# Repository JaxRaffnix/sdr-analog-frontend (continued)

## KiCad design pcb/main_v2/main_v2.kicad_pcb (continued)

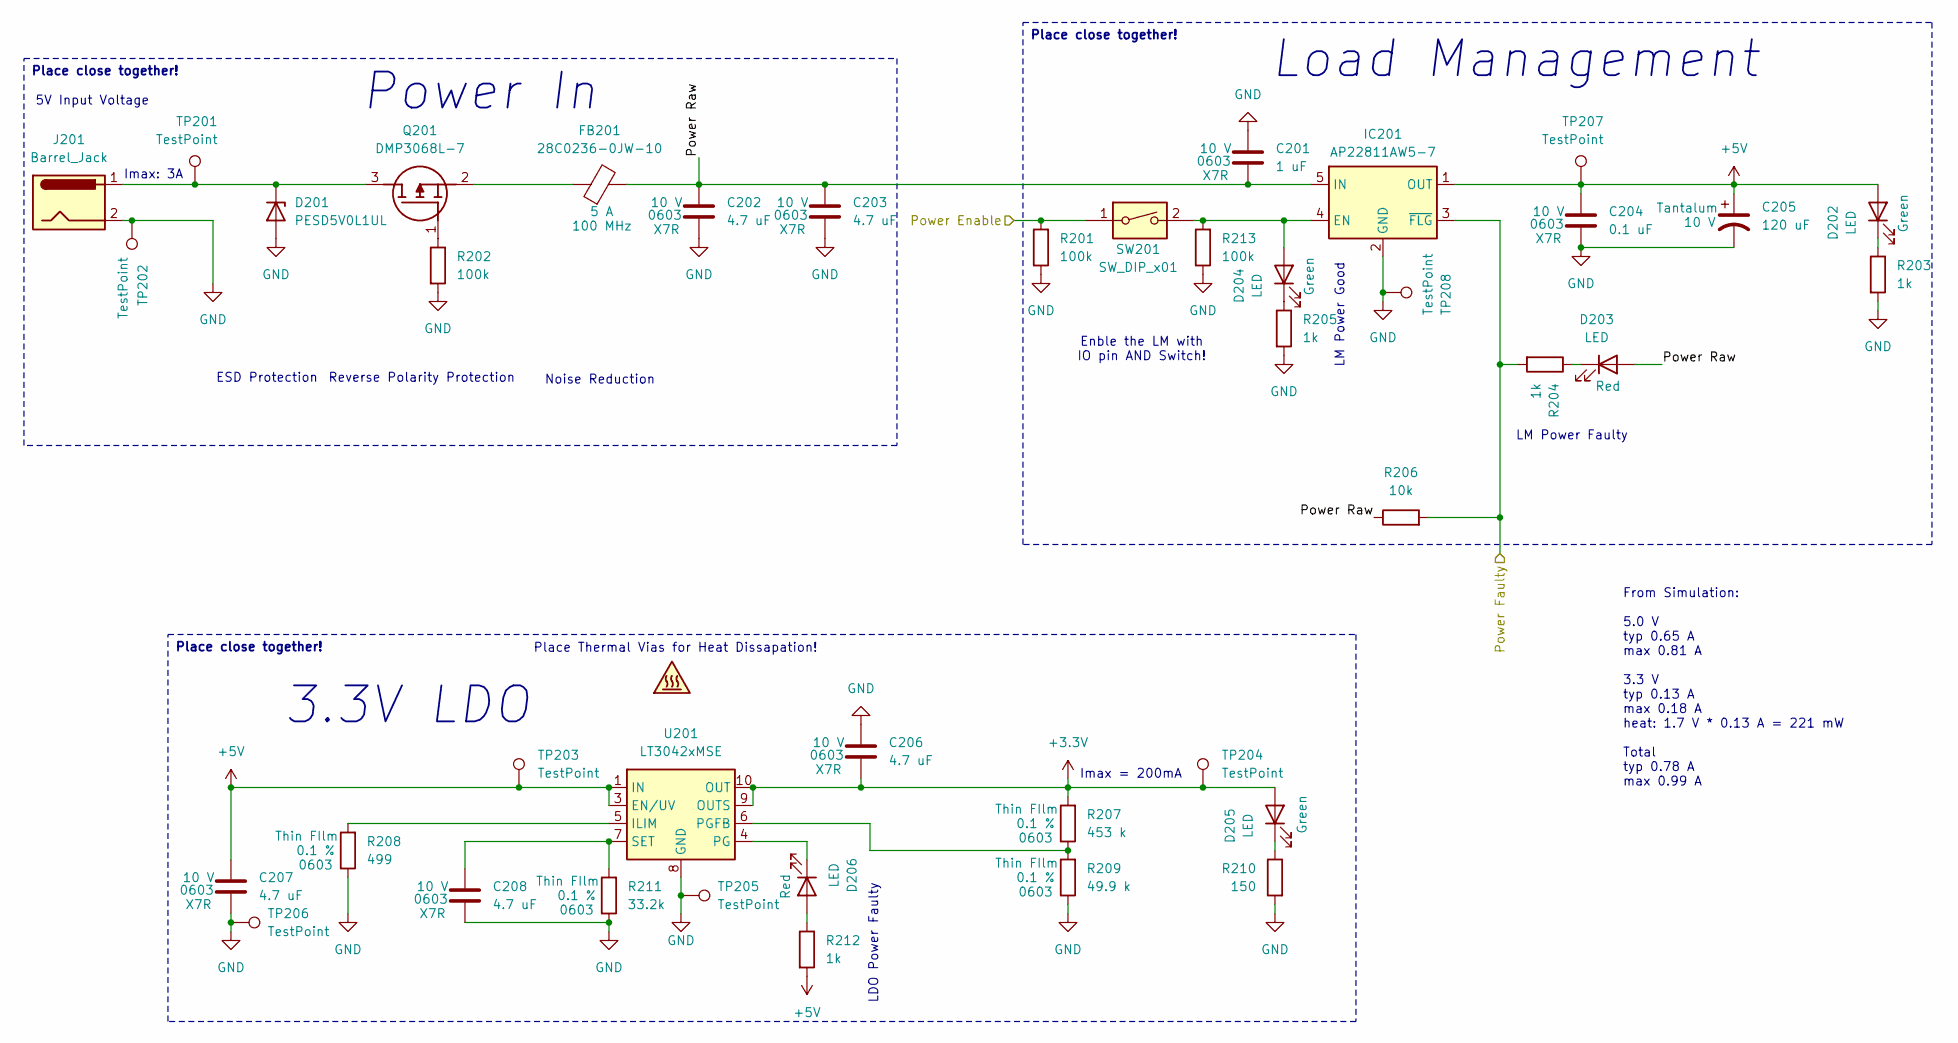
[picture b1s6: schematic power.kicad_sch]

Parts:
C201: 1 uF; C_0603_1608Metric; Voltage 10 V
C202, C203, C206, C207, C208: 4.7 uF; C_0603_1608Metric; Voltage 10 V
C204: 0.1 uF; C_0603_1608Metric; Voltage 10 V
C205: 120 uF; CP_EIA-6032-20_AVX-F; Voltage 10 V
D201: PESD5V0L1UL; D_SOD-882
D202, D203, D204, D205, D206: LED; LED_0805_2012Metric
FB201: 28C0236-0JW-10; LairdTech_28C0236-0JW-10
IC201: AP22811AW5-7; SOT-23-5; Mouser Part Number 621-AP22811AW5-7
J201: Barrel_Jack; BarrelJack_CUI_PJ-063AH_Horizontal_CircularHoles
Q201: DMP3068L-7; SOT96P240X115-3N; Mouser Part Number 621-DMP3068L-7
R201, R202, R213: 100k; R_0603_1608Metric
R203, R204, R205, R212: 1k; R_0603_1608Metric
R206: 10k; R_0603_1608Metric
R207: 453 k; R_0603_1608Metric; Tolerance 0.1 %
R208: 499; R_0603_1608Metric; Tolerance 0.1 %
R209: 49.9 k; R_0603_1608Metric; Tolerance 0.1 %
R210: 150; R_0603_1608Metric
R211: 33.2k; R_0603_1608Metric; Tolerance 0.1 %
SW201: SW_DIP_x01; SW_DIP_SPSTx01_Slide_6.7x4.1mm_W6.73mm_P2.54mm_LowProfile_J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
TP201, TP202, TP203, TP204, TP205, TP206, TP207, TP208: TestPoint; TestPoint_Pad_D1.0mm
U201: LT3042xMSE; MSOP-10-1EP_3x3mm_P0.5mm_EP1.68x1.88mm

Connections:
+3.3V: C206.2, D205.2 (A), R207.2, TP204.1 (1_1), U201.9 (OUTS), U201.10 (OUT); also elsewhere on the board
+5V: C204.1, C205.1, C207.1, D202.2 (A), IC201.1 (OUT), R212.2, TP203.1 (1_1), TP207.1 (1_1), U201.1 (IN), U201.2 (IN), U201.3 (EN/UV); also elsewhere on the board
/IO Interface/Power Enable: R201.2, SW201.1; also elsewhere on the board
/IO Interface/Power Faulty Out: IC201.3 (~FLG), R204.2, R206.2; also elsewhere on the board
/power/Power Raw: C201.2, C202.1, C203.1, D203.2 (A), FB201.2, IC201.5 (IN), R206.1
GND: C201.1, C202.2, C203.2, C204.2, C205.2, C206.1, C207.2, C208.2, D201.2 (A), IC201.2 (GND), J201.2, R201.1, R202.2, R203.2, R205.2, R208.1, R209.1, R210.2, R211.1, R213.1, TP202.1 (1_1), TP205.1 (1_1), TP206.1 (1_1), TP208.1 (1_1), U201.8 (GND), U201.11 (GND); also elsewhere on the board
unnamed: D201.1 (K), J201.1, Q201.3 (D), TP201.1 (1_1)
unnamed: D202.1 (K), R203.1
unnamed: D203.1 (K), R204.1
unnamed: D204.2 (A), IC201.4 (EN), R213.2, SW201.2
unnamed: D204.1 (K), R205.1
unnamed: D205.1 (K), R210.1
unnamed: D206.2 (A), R212.1
unnamed: D206.1 (K), U201.4 (PG)
unnamed: Q201.1 (G), R202.1
unnamed: FB201.1, Q201.2 (S)
unnamed: R208.2, U201.5 (ILIM)
unnamed: R207.1, R209.2, U201.6 (PGFB)
unnamed: C208.1, R211.2, U201.7 (SET)

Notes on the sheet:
Power In
From Simulation: 5.0 V typ 0.65 A max 0.81 A 3.3 V typ 0.13 A max 0.18 A heat: 1.7 V * 0.13 A = 221 mW Total typ 0.78 A max 0.99 A
ESD Protection
LM Power Faulty
Load Management
Imax = 200mA
3.3V LDO
LDO Power Faulty
Imax: 3A
LM Power Good
Reverse Polarity Protection
Enble the LM with IO pin AND Switch!
Place Thermal Vias for Heat Dissapation!
Noise Reduction
5V Input Voltage
Place close together!

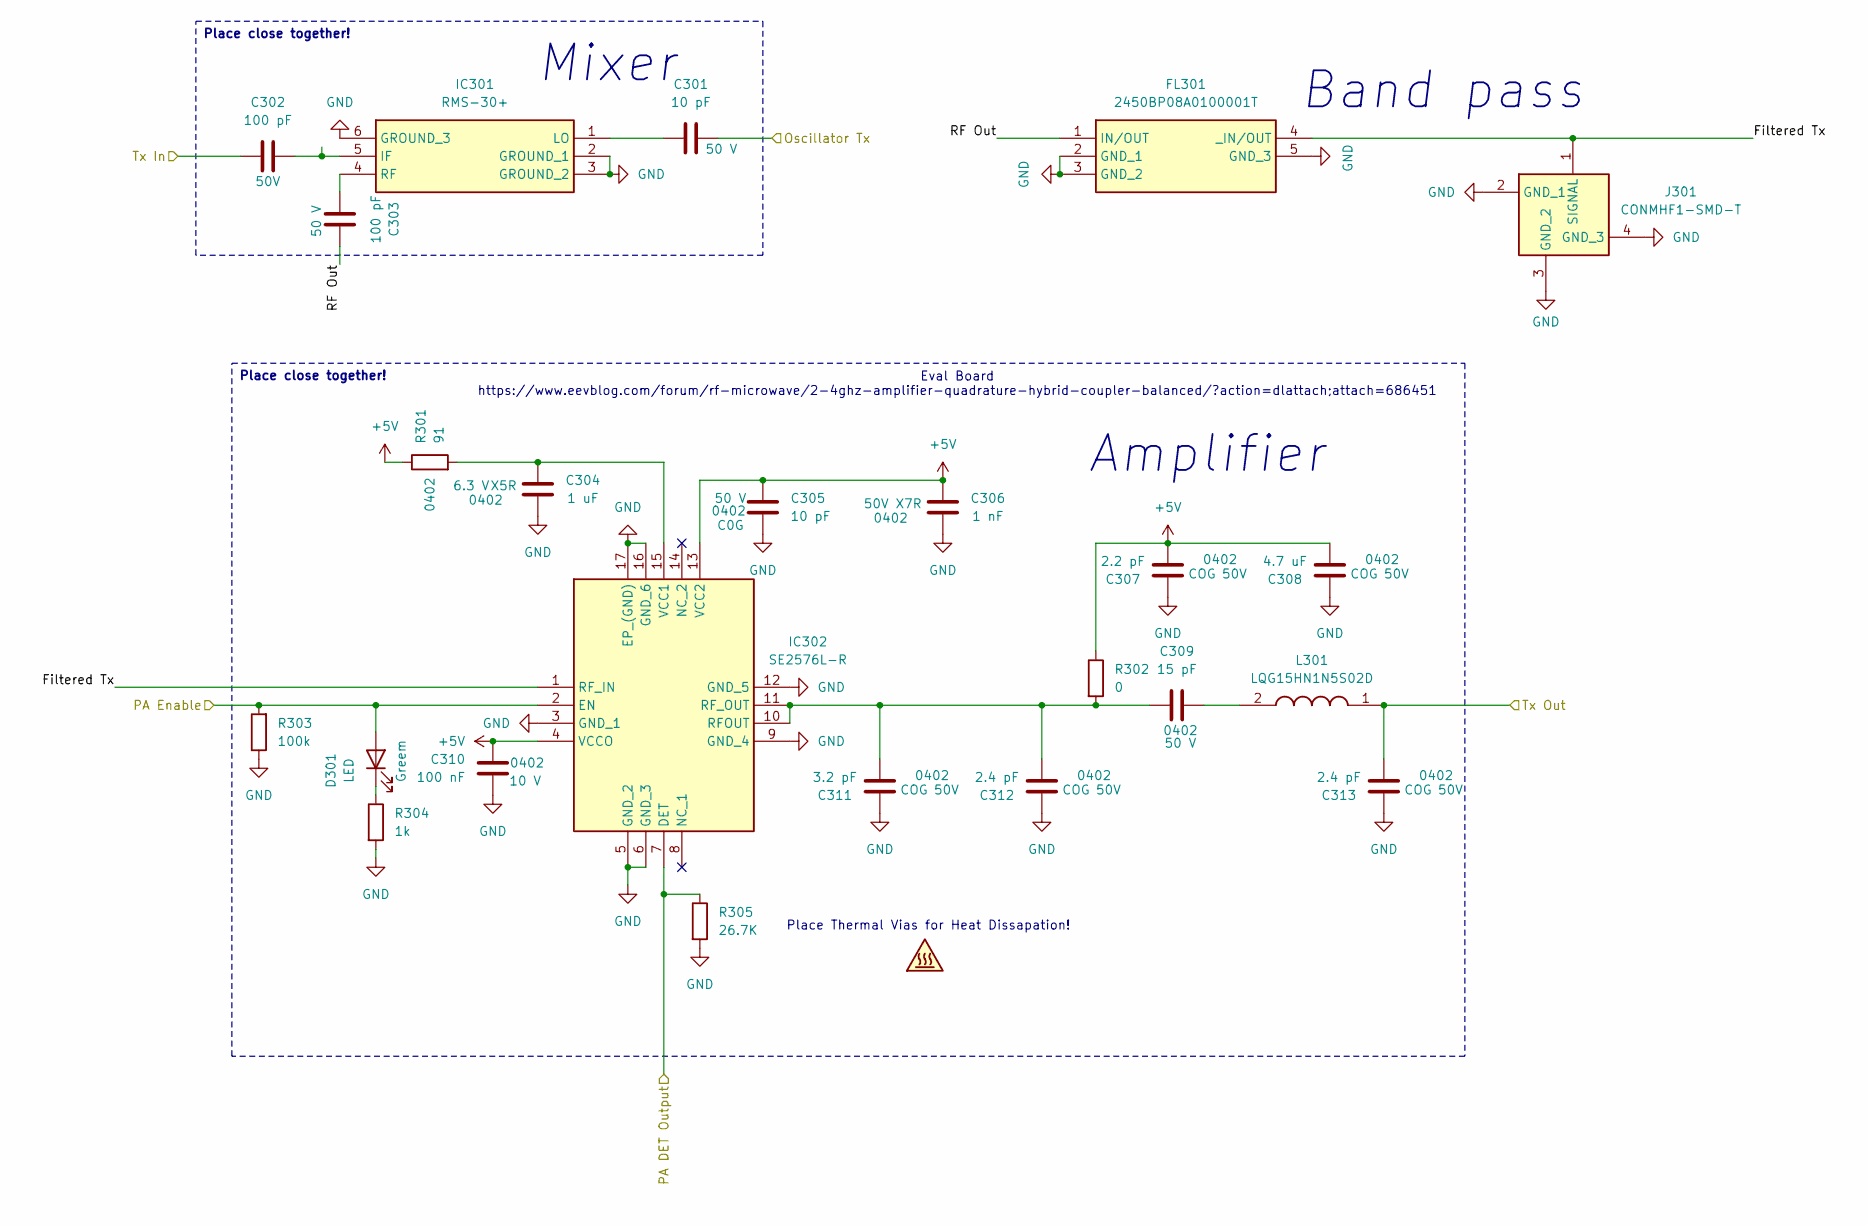
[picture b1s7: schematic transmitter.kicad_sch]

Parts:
C301, C305: 10 pF; C_0402_1005Metric; Voltage 50 V
C302: 100 pF; C_0402_1005Metric; Voltage 50V
C303: 100 pF; C_0402_1005Metric; Voltage 50 V
C304: 1 uF; C_0402_1005Metric; Tolerance 10 %; Voltage 6.3 V
C306: 1 nF; C_0402_1005Metric; Tolerance ±10%; Voltage 50V
C307: 2.2 pF; C_0402_1005Metric; Tolerance ±10%; Voltage 50V
C308: 4.7 uF; C_0402_1005Metric; Tolerance ±10%; Voltage 50V
C309: 15 pF; C_0402_1005Metric; Voltage 50 V
C310: 100 nF; C_0402_1005Metric; Tolerance 10 %; Voltage 10 V
C311: 3.2 pF; C_0402_1005Metric; Tolerance ±10%; Voltage 50V
C312, C313: 2.4 pF; C_0402_1005Metric; Tolerance ±10%; Voltage 50V
D301: LED; LED_0805_2012Metric
FL301: 2450BP08A0100001T; Manufacturer_Part_Number 2450BP08A0100001T
IC301: RMS-30+; RMS30; Manufacturer_Part_Number RMS-30+
IC302: SE2576L-R; QFN50P300X300X90-17N-D; Mouser Part Number 873-SE2576L-R
J301: CONMHF1-SMD-T; CONMHF1SMDT; Mouser Part Number 712-CONMHF1-SMD-T
L301: LQG15HN1N5S02D; LQG15WH0N7B02D; Mouser Part Number 81-LQG15HN1N5S02D
R301: 91; R_0402_1005Metric; Tolerance 5%
R302: 0; R_0603_1608Metric
R303: 100k; R_0603_1608Metric
R304: 1k; R_0603_1608Metric
R305: 26.7K; R_0603_1608Metric

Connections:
+5V: C305.1, C306.2, C307.1, C308.1, C310.1, IC302.4 (VCCO), IC302.13 (VCC2), R301.1, R302.1; also elsewhere on the board
/IO Interface/PA DET Output: IC302.7 (DET), R305.1; also elsewhere on the board
/IO Interface/PA Enable: D301.2 (A), IC302.2 (EN), R303.2; also elsewhere on the board
/Oscillator Splitter/Oscillator Tx: C301.2; also elsewhere on the board
/transmitter/Filtered Tx: FL301.4 (_IN/OUT), IC302.1 (RF_IN), J301.1 (SIGNAL)
/transmitter/RF Out: C303.2, FL301.1 (IN/OUT)
/transmitter/Tx In: C302.1; also elsewhere on the board
/transmitter/Tx Out: C313.1, L301.1; also elsewhere on the board
GND: C304.1, C305.2, C306.1, C307.2, C308.2, C310.2, C311.2, C312.2, C313.2, FL301.2 (GND_1), FL301.3 (GND_2), FL301.5 (GND_3), IC301.2 (GROUND_1), IC301.3 (GROUND_2), IC301.6 (GROUND_3), IC302.3 (GND_1), IC302.5 (GND_2), IC302.6 (GND_3), IC302.9 (GND_4), IC302.12 (GND_5), IC302.16 (GND_6), IC302.17 (EP_(GND)), J301.2 (GND_1), J301.3 (GND_2), J301.4 (GND_3), R303.1, R304.2, R305.2; also elsewhere on the board
unnamed: C309.2, L301.2
unnamed: D301.1 (K), R304.1
unnamed: C302.2, IC301.5 (IF)
unnamed: C301.1, IC301.1 (LO)
unnamed: C303.1, IC301.4 (RF)
unnamed: C309.1, C311.1, C312.1, IC302.10 (RFOUT), IC302.11 (RF_OUT), R302.2
unnamed: C304.2, IC302.15 (VCC1), R301.2

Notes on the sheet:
Place Thermal Vias for Heat Dissapation!
Eval Board https://www.eevblog.com/forum/rf-microwave/2-4ghz-amplifier-quadrature-hybrid-coupler-balanced/?action=dlattach;attach=686451
Amplifier
Mixer
Band pass
Place close together!

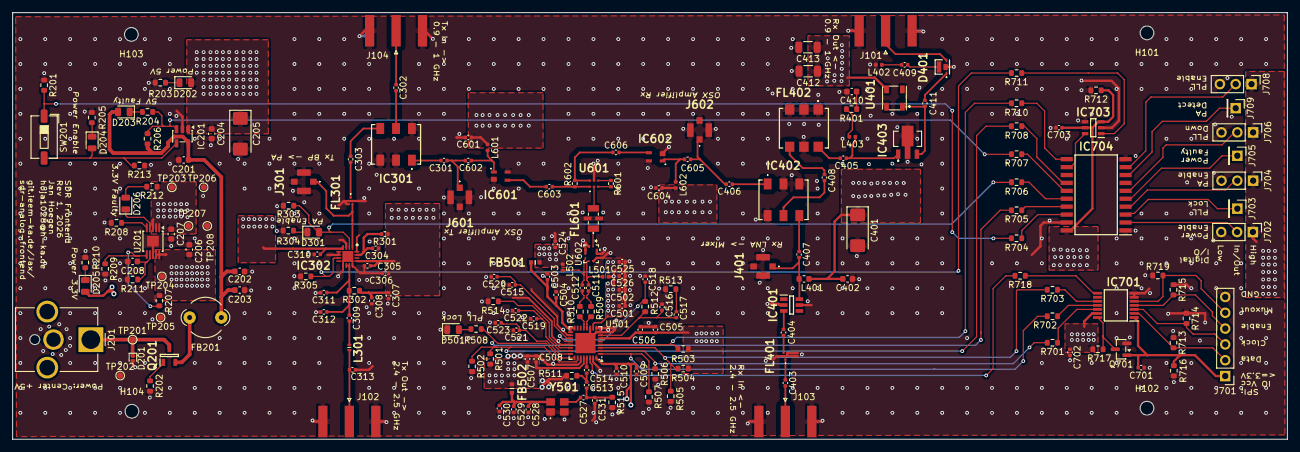
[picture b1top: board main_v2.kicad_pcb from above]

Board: 4 copper layers, 204.7 x 68.5 mm, 201 parts (0 on the bottom side), 114 nets.

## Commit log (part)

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2026-06-15 Neue Datei hochladen
2026-06-15 updated docs
2026-06-16 added schematic folder
2026-06-21 worked on layout
2026-06-29 updated layout
2026-06-29 update layout
